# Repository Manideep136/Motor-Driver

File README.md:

# Motor-Driver

Welcome to the **DRV8833 Dual H-Bridge Motor Driver** project! This repository contains open-source hardware files for a compact and reliable PCB designed to control small DC motors and stepper motors in robotics and embedded systems. 

---

## ✨ What Does This Project Do?
This circuit board acts as the "muscle" for your microcontroller (like an Arduino, ESP32, or STM32). While microcontrollers can think and process data, they cannot provide enough electrical power to drive motors directly. This board uses the **DRV8833 chip** to take low-power signals from your microcontroller and safely translate them into high-power motion for your motors.

---

## 🛠️ Key Features
- **Dual Motor Control:** Independently control the speed and direction of up to **two DC motors** (or one stepper motor).
- **Built-In Safety:** Features internal overcurrent protection, short-circuit protection, and thermal shutdown to prevent the board from burning out.
- **Low Voltage Operation:** Works smoothly with low-voltage power supplies (ranging from 2.7V to 10.8V).
- **PWM Speed Control:** Allows smooth speed variations using Pulse Width Modulation signals.

---

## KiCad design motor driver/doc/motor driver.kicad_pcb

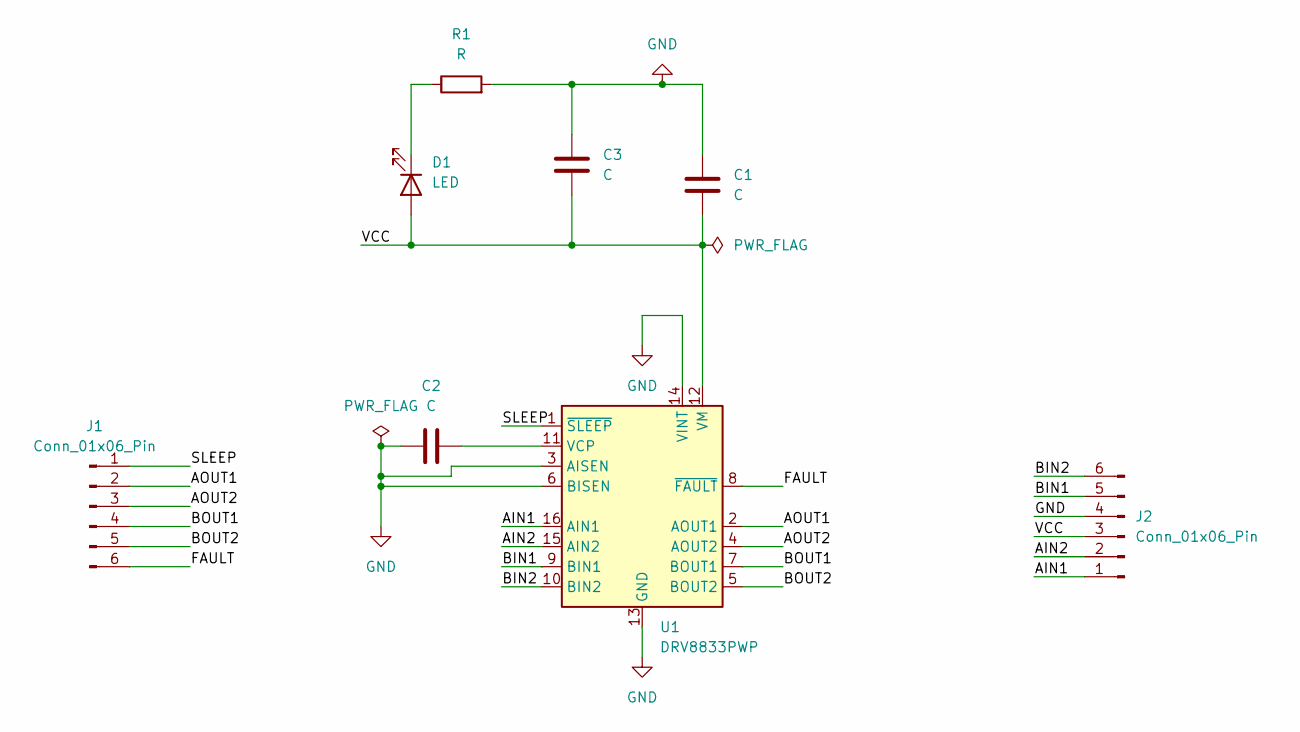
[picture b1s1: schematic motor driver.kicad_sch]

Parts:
C1, C2: C; C_0805_2012Metric
C3: C; CP_EIA-6032-20_AVX-F
D1: LED; LED_0805_2012Metric
J1, J2: Conn_01x06_Pin; PinHeader_1x06_P2.54mm_Vertical
R1: R; R_0805_2012Metric
U1: DRV8833PWP; HTSSOP-16-1EP_4.4x5mm_P0.65mm_EP3.4x5mm_Mask2.46x2.31mm_The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

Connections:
/AIN1: J2.1, U1.16 (AIN1)
/AIN2: J2.2, U1.15 (AIN2)
/AOUT1: J1.2, U1.2 (AOUT1)
/AOUT2: J1.3, U1.4 (AOUT2)
/BIN1: J2.5, U1.9 (BIN1)
/BIN2: J2.6, U1.10 (BIN2)
/BOUT1: J1.4, U1.7 (BOUT1)
/BOUT2: J1.5, U1.5 (BOUT2)
/FAULT: J1.6, U1.8 (~FAULT)
/SLEEP: J1.1, U1.1 (~SLEEP)
/VCC: C1.2, C3.1, D1.2 (A), J2.3, U1.12 (VM)
GND: C1.1, C2.1, C3.2, J2.4, R1.2, U1.3 (AISEN), U1.6 (BISEN), U1.13 (GND), U1.14 (VINT), U1.17 (GND)
unnamed: D1.1 (K), R1.1
unnamed: C2.2, U1.11 (VCP)

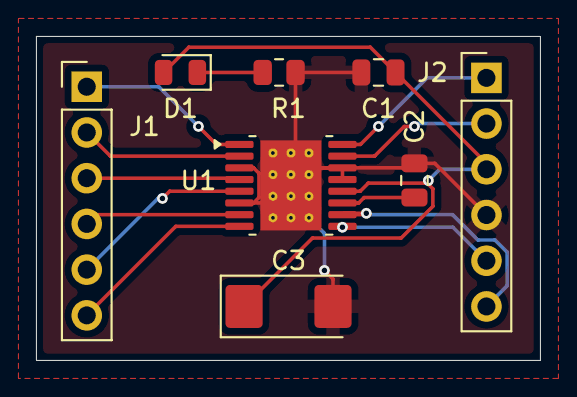
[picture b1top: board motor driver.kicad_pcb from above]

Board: 2 copper layers, 28.0 x 18.0 mm, 8 parts (0 on the bottom side), 14 nets.
